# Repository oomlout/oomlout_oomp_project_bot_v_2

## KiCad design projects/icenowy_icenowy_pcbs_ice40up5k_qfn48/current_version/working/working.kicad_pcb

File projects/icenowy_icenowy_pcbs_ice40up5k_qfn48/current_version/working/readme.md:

# icenowy_pcbs
 
## summary 
* id: icenowy_icenowy_pcbs_ice40up5k_qfn48
* user: icenowy
* name: icenowy_pcbs
* board: ice40up5k_qfn48
* repo: https://github.com/Icenowy/Icenowy-PCBs
* src_file_repo_kicad_pcb: icecream_v1/ice40up5k-qfn48.kicad_pcb
* src_file_repo_kicad_pcb_link: https://github.com/Icenowy/Icenowy-PCBs/tree/master/icecream_v1/ice40up5k-qfn48.kicad_pcb

* src_file_repo_sch: icecream_v1/ice40up5k-qfn48.sch
* src_file_repo_sch_link: https://github.com/Icenowy/Icenowy-PCBs/tree/master/icecream_v1/ice40up5k-qfn48.sch
* full details link: https://github.com/oomlout/oomlout_oomp_project_bot_v_2/tree/main/projects/icenowy_icenowy_pcbs_ice40up5k_qfn48/current_version/working

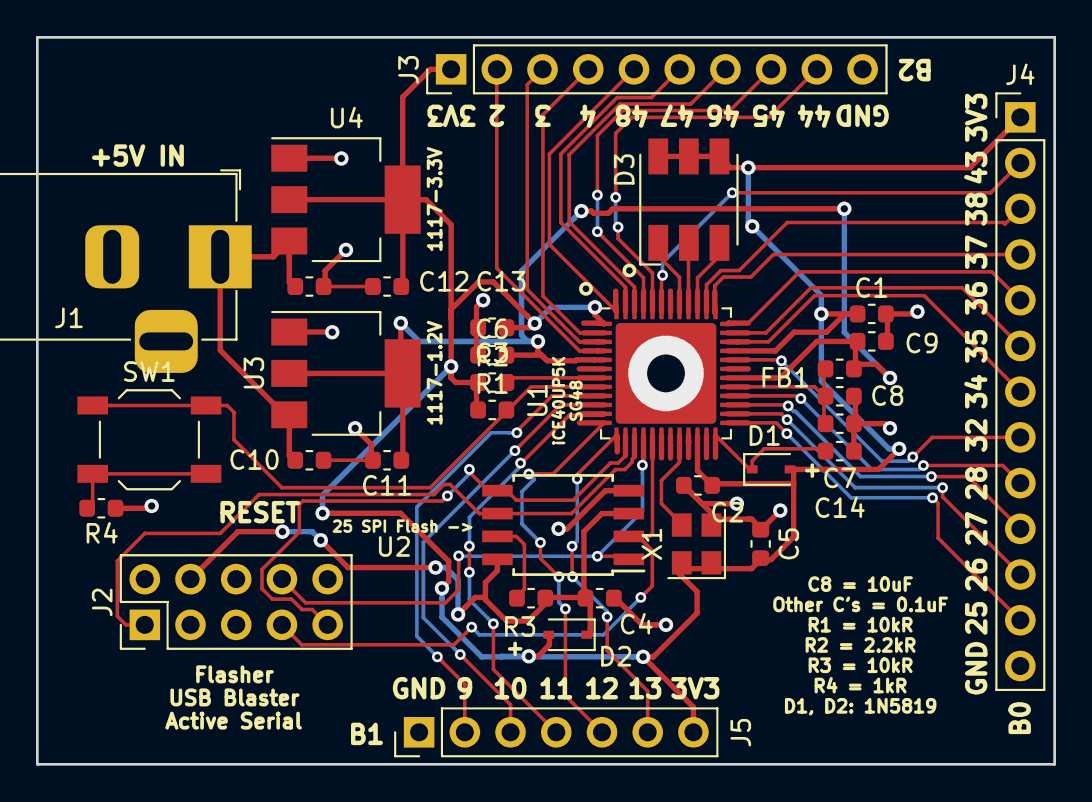
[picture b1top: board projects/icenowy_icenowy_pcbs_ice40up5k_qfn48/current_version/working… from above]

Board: 2 copper layers, 56.5 x 40.4 mm, 33 parts (0 on the bottom side), 43 nets.

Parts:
C1, C2, C3, C4, C5, C6, C7, C9, C10, C11, C12, C13, C14: 0.1uF; C_0603_1608Metric
C8: 10uF; C_0603_1608Metric
D1, D2: 1N5819; D_SOD-323
D3: LED_RGB; LED_RGB_5050-6
FB1: Ferrite_Bead; L_0603_1608Metric
J1: 5V 3.5mm/1.35mm; BarrelJack_Horizontal
J2: Flasher; PinHeader_2x05_P2.54mm_Vertical
J3: Bank 2; PinHeader_1x10_P2.54mm_Vertical
J4: Bank 0; PinHeader_1x13_P2.54mm_Vertical
J5: Bank 1; PinHeader_1x07_P2.54mm_Vertical
R1, R3: 10kR; R_0603_1608Metric
R2: 2.2kR; R_0603_1608Metric
R4: 1kR; R_0603_1608Metric
SW1: Button; SW_SPST_TL3342
U1: ICE40UP5K-SG48ITR; QFN-48-1EP_7x7mm_P0.5mm_EP5.6x5.6mm
U2: W25Q80; SOIJ-8_5.3x5.3mm_P1.27mm
U3: LD1117S12TR_SOT223; SOT-223-3_TabPin2
U4: LD1117S33TR_SOT223; SOT-223-3_TabPin2
X1: 50MHz; Oscillator_SMD_Abracon_ASE-4Pin_3.2x2.5mm

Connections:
+1V2: C6.2, C9.2, C11.1, FB1.1, U1.5, U1.30, U3.2
+3.3VP: C4.1, D2.1, J2.4, R3.1, U2.3, U2.8
+3V3: C1.1, C2.1, C3.1, C5.1, C13.1, D1.2, D2.2, D3.4, D3.5, D3.6, J3.1, J4.1, J5.7, R1.1, R2.1, U1.1, U1.22, U1.33, U4.2, X1.1, X1.4
+5V: C10.1, C12.1, J1.1, U3.3, U4.3
/2: J3.4, U1.2
/3: J3.3, U1.3
/4: J3.2, U1.4
/9: J5.2, U1.9
/10: J5.3, U1.10
/11: J5.4, U1.11
/12: J5.5, U1.12
/13: J5.6, U1.13
/25: J4.12, U1.25
/26: J4.11, U1.26
/27: J4.10, U1.27
/28: J4.9, U1.28
/32: J4.8, U1.32
/34: J4.7, U1.34
/35: J4.6, U1.35
/36: J4.5, U1.36
/37: J4.4, U1.37
/38: J4.3, U1.38
/43: J4.2, U1.43
/44: J3.9, U1.44
/45: J3.8, U1.45
/46: J3.7, U1.46
/47: J3.6, U1.47
/48: J3.5, U1.48
/CDONE: R2.2, U1.7
/CLK_50M: U1.20, X1.3
/CRESET: R1.2, SW1.1, U1.8
/ICE_SCK: J2.1, U1.15, U2.6
/ICE_SI: J2.7, U1.17, U2.2
/ICE_SO: J2.9, U1.14, U2.5
/ICE_SS: J2.8, U1.16, U2.1
GND: C1.2, C2.2, C3.2, C4.2, C5.2, C6.1, C7.1, C8.1, C9.1, C10.2, C11.2, C12.2, C13.2, C14.2, J1.2, J2.2, J2.10, J3.10, J4.13, J5.1, R4.1, U1.49, U2.4, U3.1, U4.1, X1.2
unnamed: C7.2, C8.2, FB1.2, U1.29
unnamed: C14.1, D1.1, U1.24
unnamed: D3.1, U1.41
unnamed: D3.2, U1.40
unnamed: D3.3, U1.39
unnamed: R3.2, U2.7
unnamed: R4.2, SW1.2

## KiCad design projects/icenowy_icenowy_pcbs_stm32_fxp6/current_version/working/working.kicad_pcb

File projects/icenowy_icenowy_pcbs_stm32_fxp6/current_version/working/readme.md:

# icenowy_pcbs
 
## summary 
* id: icenowy_icenowy_pcbs_stm32_fxp6
* user: icenowy
* name: icenowy_pcbs
* board: stm32_fxp6
* repo: https://github.com/Icenowy/Icenowy-PCBs
* src_file_repo_kicad_pcb: stm32_fxp6/stm32_fxp6.kicad_pcb
* src_file_repo_kicad_pcb_link: https://github.com/Icenowy/Icenowy-PCBs/tree/master/stm32_fxp6/stm32_fxp6.kicad_pcb

* src_file_repo_sch: stm32_fxp6/stm32_fxp6.sch
* src_file_repo_sch_link: https://github.com/Icenowy/Icenowy-PCBs/tree/master/stm32_fxp6/stm32_fxp6.sch
* full details link: https://github.com/oomlout/oomlout_oomp_project_bot_v_2/tree/main/projects/icenowy_icenowy_pcbs_stm32_fxp6/current_version/working

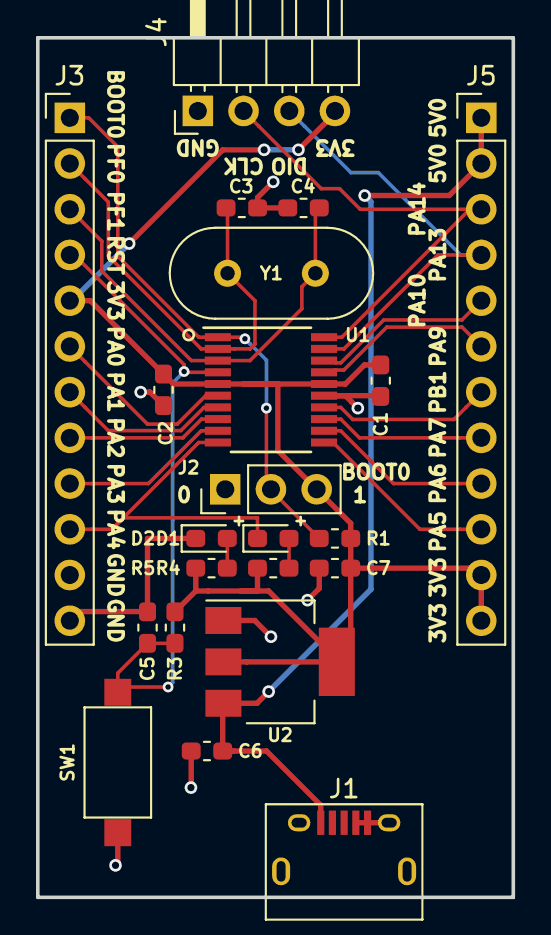
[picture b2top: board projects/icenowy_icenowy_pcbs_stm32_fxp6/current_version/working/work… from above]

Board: 2 copper layers, 26.4 x 47.8 mm, 22 parts (0 on the bottom side), 22 nets.

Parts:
C1, C2, C5, C6, C7: 0.1uF; C_0603_1608Metric_Pad1.05x0.95mm_HandSolder
C3, C4: 20pF; C_0603_1608Metric_Pad1.05x0.95mm_HandSolder
D1: GREEN; LED_0603_1608Metric_Pad1.05x0.95mm_HandSolder
D2: RED; LED_0603_1608Metric_Pad1.05x0.95mm_HandSolder
J1: USB_B_Micro; USB_Micro-B_Connector
J2: BOOT0; PinHeader_1x03_P2.54mm_Vertical
J3: LEFT; PinHeader_1x12_P2.54mm_Vertical
J4: SWD; PinHeader_1x04_P2.54mm_Horizontal
J5: RIGHT; PinHeader_1x12_P2.54mm_Vertical
R1, R3: 10kR; R_0603_1608Metric_Pad1.05x0.95mm_HandSolder
R4, R5: 1.5kR; R_0603_1608Metric_Pad1.05x0.95mm_HandSolder
SW1: SW_Push; SW_SPST_CK_RS282G05A3
U1: STM32F042F6Px; TSSOP-20_4.4x6.5mm_P0.65mm
U2: 1117-3.3; SOT-223-3_TabPin2
Y1: 8MHz; Crystal_HC49-U_Vertical

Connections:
/BOOT0: J2.2, J3.1, R1.1, U1.1
/NRST: C5.1, J3.4, R3.2, SW1.1, U1.4
/OSC_IN: C3.2, J3.2, U1.2, Y1.1
/OSC_OUT: C4.2, J3.3, U1.3, Y1.2
/PA0: J3.6, U1.6
/PA1: J3.7, U1.7
/PA2: J3.8, U1.8
/PA3: J3.9, U1.9
/PA4: D1.1, J3.10, U1.10
/PA5: J5.10, U1.11
/PA6: J5.9, U1.12
/PA7: J5.8, U1.13
/PA9_PA11: J5.6, U1.17
/PA10_PA12: J5.5, U1.18
/PA13: J4.3, J5.4, U1.19
/PA14: J4.2, J5.3, U1.20
/PB1: J5.7, U1.14
GND: C1.1, C2.1, C3.1, C4.1, C5.2, C6.1, C7.2, D2.1, J1.4, J1.5, J1.6, J2.1, J3.11, J3.12, J4.1, SW1.2, U1.15, U2.1
unnamed: D1.2, R4.2
unnamed: D2.2, R5.2
VBUS: C6.2, J1.1, J5.1, J5.2, U2.3
VCC: C1.2, C2.2, C7.1, J2.3, J3.5, J4.4, J5.11, J5.12, R1.2, R3.1, R4.1, R5.1, U1.5, U1.16, U2.2

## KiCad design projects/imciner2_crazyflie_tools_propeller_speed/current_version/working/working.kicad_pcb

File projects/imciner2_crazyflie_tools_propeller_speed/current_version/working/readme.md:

# crazyflie_tools
 
## summary 
* id: imciner2_crazyflie_tools_propeller_speed
* user: imciner2
* name: crazyflie_tools
* board: propeller_speed
* repo: https://github.com/imciner2/Crazyflie_Tools
* src_file_repo_kicad_pcb: PropellerSpeed_Hardware/2-Hardware/KiCad-Project/Propeller_Speed.kicad_pcb
* src_file_repo_kicad_pcb_link: https://github.com/imciner2/Crazyflie_Tools/tree/master/PropellerSpeed_Hardware/2-Hardware/KiCad-Project/Propeller_Speed.kicad_pcb

* src_file_repo_sch: PropellerSpeed_Hardware/2-Hardware/KiCad-Project/Propeller_Speed.sch
* src_file_repo_sch_link: https://github.com/imciner2/Crazyflie_Tools/tree/master/PropellerSpeed_Hardware/2-Hardware/KiCad-Project/Propeller_Speed.sch
* full details link: https://github.com/oomlout/oomlout_oomp_project_bot_v_2/tree/main/projects/imciner2_crazyflie_tools_propeller_speed/current_version/working

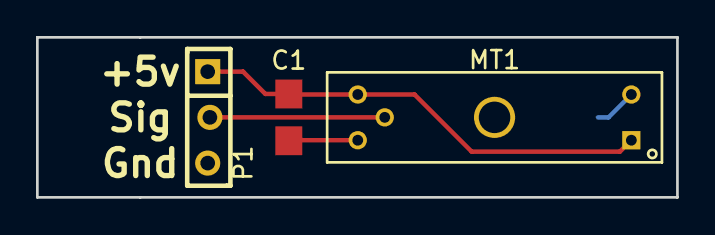
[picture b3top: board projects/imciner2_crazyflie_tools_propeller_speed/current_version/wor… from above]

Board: 2 copper layers, 35.6 x 8.9 mm, 4 parts (1 on the bottom side), 4 nets.

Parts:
C1: 0.1u; SMD_0805
MT1: GP1A57HRJ00F; SHARP_GP1A57HRJ00F
P1: CONN_1x3; CONN_2.54mm_1x3
R1: 470; SMD_0805

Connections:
/GND: C1.2, MT1.5, P1.3, R1.2
/Vcc: C1.1, MT1.1, MT1.3, P1.1
unnamed: MT1.2, R1.1
unnamed: MT1.4, P1.2
